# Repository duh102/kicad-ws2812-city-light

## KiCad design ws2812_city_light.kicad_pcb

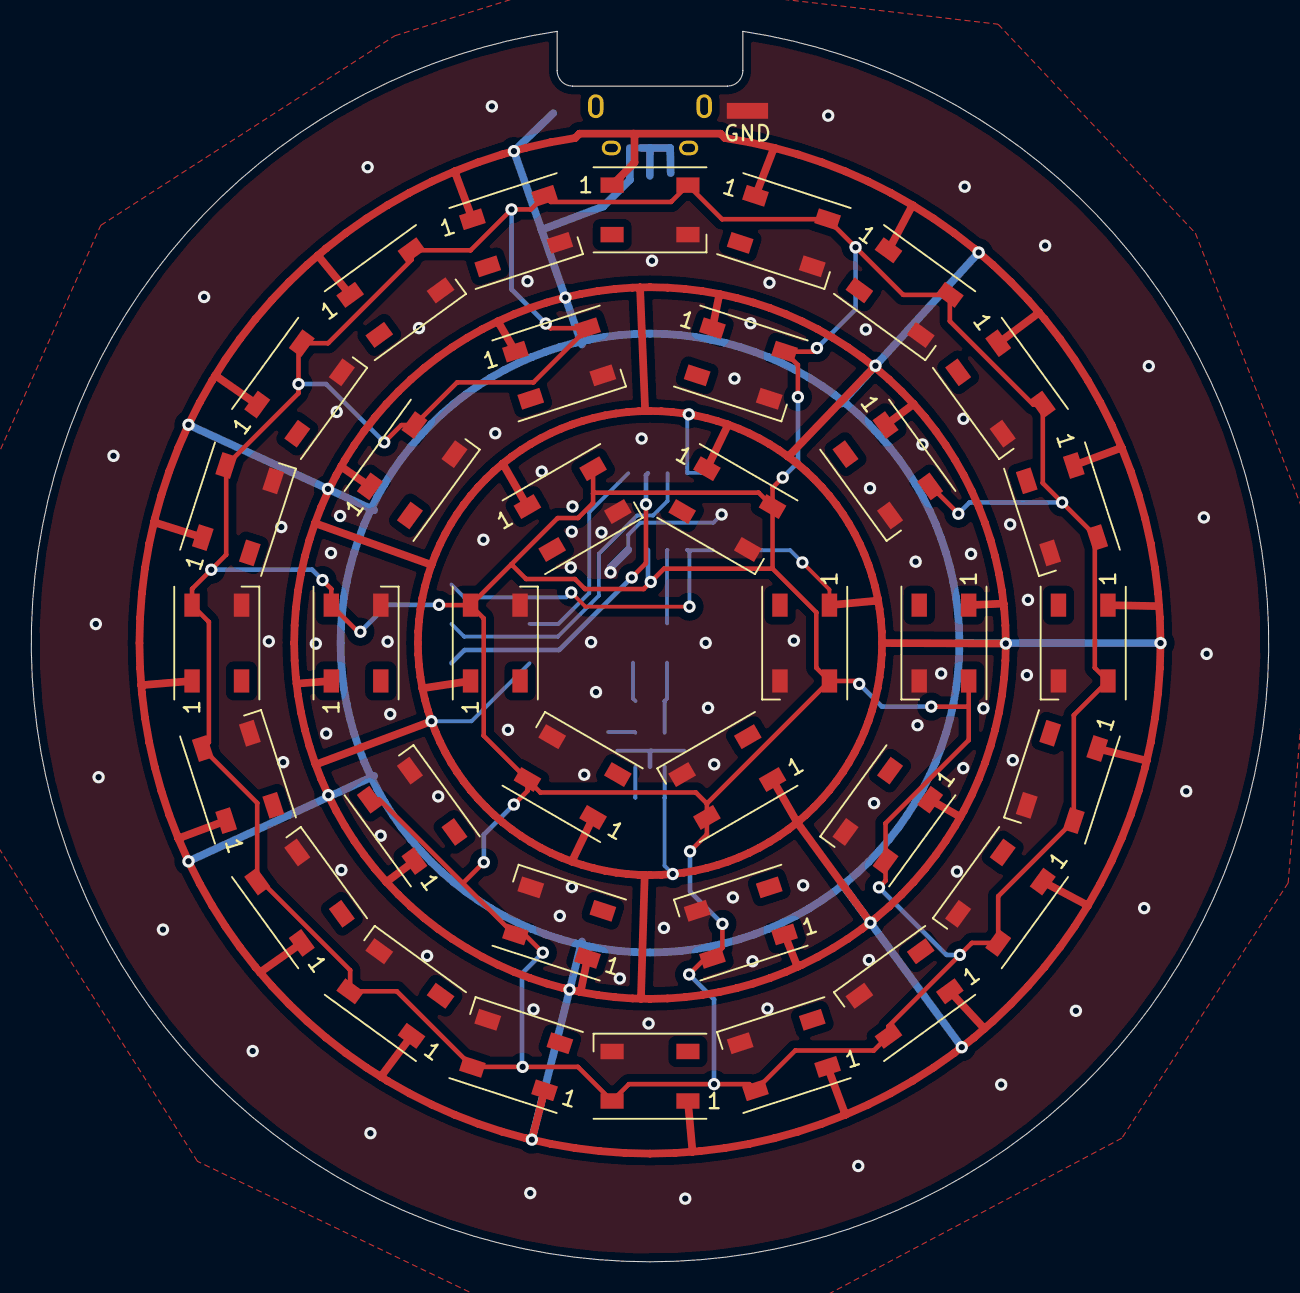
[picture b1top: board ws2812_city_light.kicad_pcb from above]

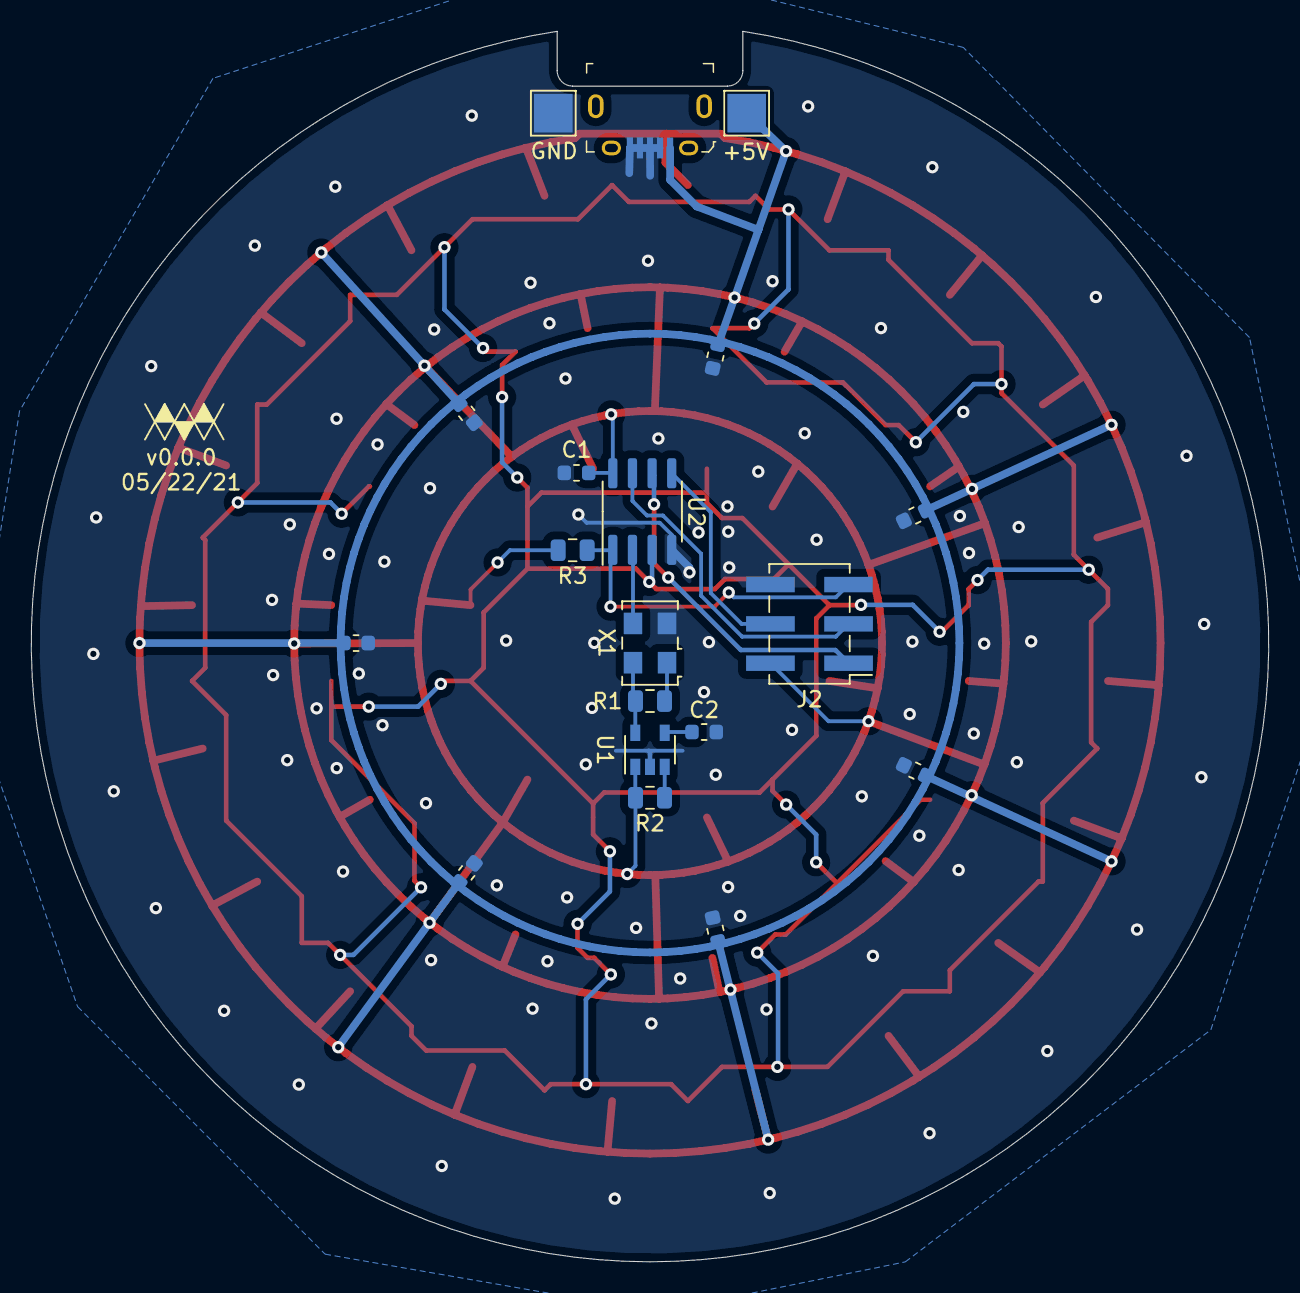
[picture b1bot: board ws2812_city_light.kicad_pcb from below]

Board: 2 copper layers, 80.0 x 79.5 mm, 56 parts (19 on the bottom side), 12 nets.

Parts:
C1, C2, C3: 10kpF; C_0603_1608Metric
C4, C5, C6, C7, C8, C9: C_Small; C_0603_1608Metric
D1, D2, D3, D4, D5, D6, D7, D8, D9, D10, D11, D12, D13, D14, D15, D16, D17, D18, D19, D20, D21, D22, D23, D24, D25, D26, D27, D28, D29, D30, D31, D32, D33, D34, D35, D36: WS2812B; LED_WS2812B_PLCC4_5.0x5.0mm_P3.2mm
GND: Test_Point_2.67x1.02mm
J1: USB_B_Micro; USB_Micro_B_Female_10118194-0001LF
J2: AVR-ISP-6; PinHeader_2x03_P2.54mm_Vertical_SMD
R1, R2, R3: 10kR; R_0805_2012Metric
TP1: +5V; TestPoint_Pad_2.5x2.5mm
TP2: GND; TestPoint_Pad_2.5x2.5mm
U1: TC2014-3.3VxCTTR; SOT-23-5
U2: ATtiny13A-SSU; SOIC-8_3.9x4.9mm_P1.27mm
X1: SXO-53C3A071; Oscillator_SMD_TXC_7C-4Pin_5.0x3.2mm

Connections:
20MHZ: U2.2, X1.3
+3.3V: R1.2, U1.5, X1.4
+5V: C1.1, C3.1, C4.1, C5.1, C6.1, C7.1, C8.1, C9.1, D1.1, D2.1, D3.1, D4.1, D5.1, D6.1, D7.1, D8.1, D9.1, D10.1, D11.1, D12.1, D13.1, D14.1, D15.1, D16.1, D17.1, D18.1, D19.1, D20.1, D21.1, D22.1, D23.1, D24.1, D25.1, D26.1, D27.1, D28.1, D29.1, D30.1, D31.1, D32.1, D33.1, D34.1, D35.1, D36.1, J1.1, J2.2, R2.2, R3.2, TP1.1, U1.1, U2.8
DOUT: D1.4, D2.4, D3.4, D4.4, D5.4, D6.4, D7.4, D8.4, D9.4, D10.4, D11.4, D12.4, D13.4, D14.4, D15.4, D16.4, D17.4, D18.4, D19.4, D20.4, D21.4, D22.4, D23.4, D24.4, D25.4, D26.4, D27.4, D28.4, D29.4, D30.4, D31.4, D32.4, D33.4, D34.4, D35.4, D36.4, U2.3
GND: C1.2, C2.2, C3.2, C4.2, C5.2, C6.2, C7.2, C8.2, C9.2, D1.3, D2.3, D3.3, D4.3, D5.3, D6.3, D7.3, D8.3, D9.3, D10.3, D11.3, D12.3, D13.3, D14.3, D15.3, D16.3, D17.3, D18.3, D19.3, D20.3, D21.3, D22.3, D23.3, D24.3, D25.3, D26.3, D27.3, D28.3, D29.3, D30.3, D31.3, D32.3, D33.3, D34.3, D35.3, D36.3, GND.1, J1.2, J1.3, J1.4, J1.5, J2.6, TP2.1, U1.2, U2.4, X1.2
MISO: J2.1, U2.6
MOSI: J2.4, U2.5
unnamed: C2.1, U1.4
unnamed: R1.1, X1.1
unnamed: R2.1, U1.3
RESET: J2.5, R3.1, U2.1
SCK: J2.3, U2.7

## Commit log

2021-11-11 Initial commit; fully working
